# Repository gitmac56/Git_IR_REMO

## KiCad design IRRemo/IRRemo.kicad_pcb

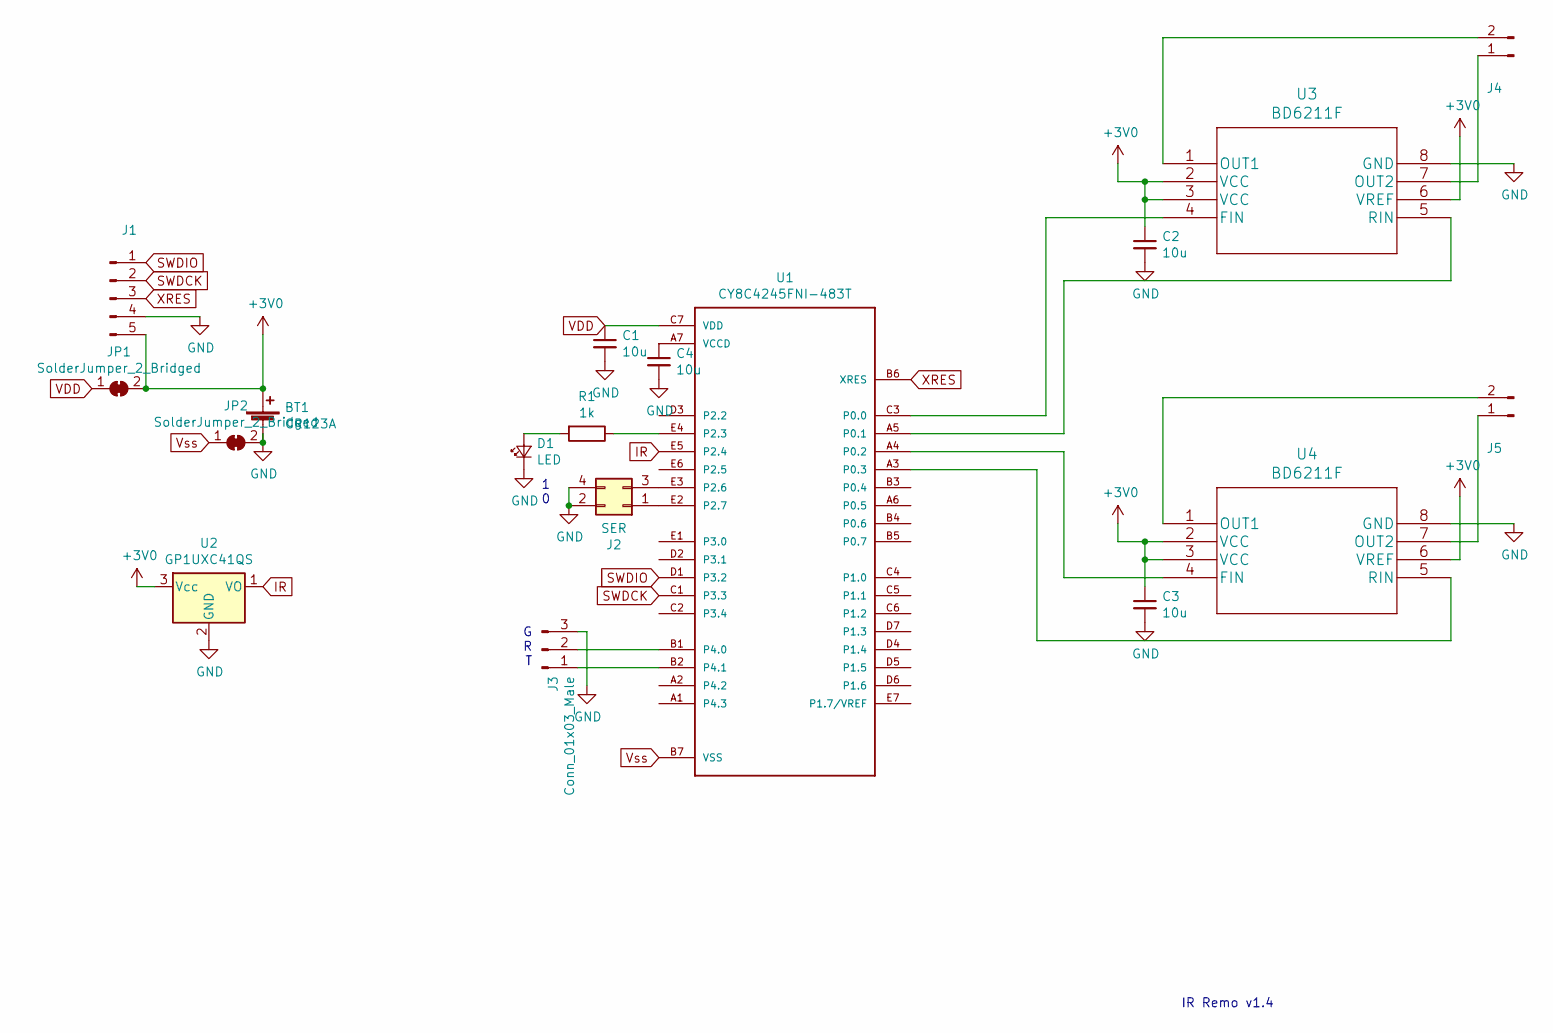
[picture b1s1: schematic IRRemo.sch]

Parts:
BT1: CR123A; BatteryHolder_BHC-CR123A
C1, C2, C3, C4: 10u; C_0603_1608Metric
D1: LED; LED_0603_1608Metric
J1: Conn_01x05_Male; PinHeader_1x05_P2.54mm_Vertical
J2: SER; PinHeader_2x02_P2.00mm_Vertical
J3: Conn_01x03_Male; PinHeader_1x03_P2.54mm_Vertical
J4, J5: Conn_01x02_Male; PinSocket_1x02_P2.00mm_Vertical
JP1, JP2: SolderJumper_2_Bridged; Jumper-Con
R1: 1k; R_0603_1608Metric_Pad1.05x0.95mm_HandSolder
U1: CY8C4245FNI-483T; BGA35N35P7X5_258X209X48N
U2: GP1UXC41QS; TO-220-3_Vertical
U3, U4: BD6211F; SO-8_5.3x6.2mm_P1.27mm

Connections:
+3V0: BT1.1 (+), C2.1, C3.1, J1.5, JP1.2 (B), U2.3 (Vcc), U3.2 (VCC), U3.3 (VCC), U3.6 (VREF), U4.2 (VCC), U4.3 (VCC), U4.6 (VREF)
GND: BT1.2 (-), C1.2, C2.2, C3.2, C4.2, D1.1 (K), J1.4, J2.2, J2.4, J3.3, JP2.2 (B), U2.2 (GND), U3.8 (GND), U4.8 (GND)
IR: U1.E5 (P2.4), U2.1 (VO)
unnamed: C4.1, U1.A7 (VCCD)
unnamed: D1.2 (A), R1.2
unnamed: J2.1, U1.E2 (P2.7)
unnamed: J2.3, U1.E3 (P2.6)
unnamed: J3.1, U1.B2 (P4.1)
unnamed: J3.2, U1.B1 (P4.0)
unnamed: J4.1, U3.7 (OUT2)
unnamed: J4.2, U3.1 (OUT1)
unnamed: J5.1, U4.7 (OUT2)
unnamed: J5.2, U4.1 (OUT1)
unnamed: R1.1, U1.E4 (P2.3)
unnamed: U1.A3 (P0.3), U4.5 (RIN)
unnamed: U1.A4 (P0.2), U4.4 (FIN)
unnamed: U1.A5 (P0.1), U3.5 (RIN)
unnamed: U1.C3 (P0.0), U3.4 (FIN)
SWDCK: J1.2, U1.C1 (P3.3)
SWDIO: J1.1, U1.D1 (P3.2)
VDD: C1.1, JP1.1 (A), U1.C7 (VDD)
Vss: JP2.1 (A), U1.B7 (VSS)
XRES: J1.3, U1.B6 (XRES)

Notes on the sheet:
1 0
IR Remo v1.4
G R T

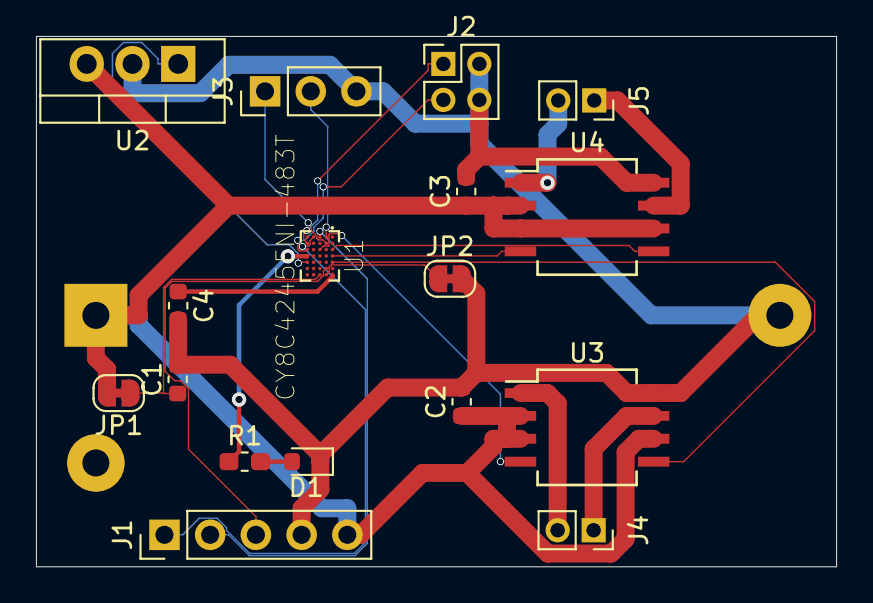
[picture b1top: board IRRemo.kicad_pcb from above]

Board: 2 copper layers, 44.5 x 29.5 mm, 18 parts (1 on the bottom side), 23 nets.

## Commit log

2020-08-19 book
    book
2020-08-19 デコード成功
2020-08-20 精度向上
2020-08-21 Renew PCB
2020-09-14 V1.5
